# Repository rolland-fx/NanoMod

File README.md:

# NanoMod

## Main goal and design

- very low power remote sensors platform
- Modular design in layers (physical layers !) : 
	- Alim + power managment + hardware watchdog 
	- Main CPU and Radio
	- Sensors
	- Any others layer

## Few design ideas 

-  I2 Cbus as inter-layer bus (SPI vs I2C debate, go !)
	- Pintout Could be :
		* I2C (2 pins)
		* Alim (2 3.3V + 2*GND)
		* M-CPU to power managmement coms (4 Sig + 2 UART)
	- Put as 2*8 connectors (2*4 pins connectors)
- Each layer will have the sames pin-out (I2C, Alims, Vbat, and a few others signals) to be able to add as much as needed
- Main CPU may have Wifi capabilites as first time config channel.
	- Wifi could be active to enable first time boot settings
	- After that, depending of the main CPU code, it could go offline (until button press to reset seetings) 
	to keep only Lora as Radio.
- Multiple 3.3V rails, to enable or disable each ones (Main 3.3V, Main CPU 3.3V and Sensors 3.3V)
- Alim input to be able to accept anything between 3.4V and 9V, with input voltage reading
- Default Power module as : two 2.7V supercapacitor in series + solar pannel (+ wathever regulator needed between the two).
	- In test system : two 478-10027-ND + S7V7F5

## Layers :
 
 ### layer 1 : 
- ATTINY814-SSF-ND --- Power managment
- ATTINY402-SSF-ND --- Hardware watchdog 
- 3*MIC5528-3.3YMT ---  Very efficient, with OFF 3.3V switch regulator
- very low current voltage divided (/3) for battery reading

### Layer 2 : 
- RFM95W-868S2-ND  --- Lora Module 

the main CPU could be whatever we want, as much as it as SPI. First version choice could be one of this two 
- ESP8285 wathever module -- Main CPU
OR
- ESP32 (V1 or V2) whatever module  -- Main CPU

Com between MCU and Radio in SPI

### Layer 3 :
- BME680 --- Sensor
- VEML6040 --- Sensor

Could like like that :

just a lot less moche !

### MCU needed features :

- UART + 2*GPIO
- SPI
- I2C
- full 3.3V
- less than 400mW full conso
- able to be alim shutdown (when ready)

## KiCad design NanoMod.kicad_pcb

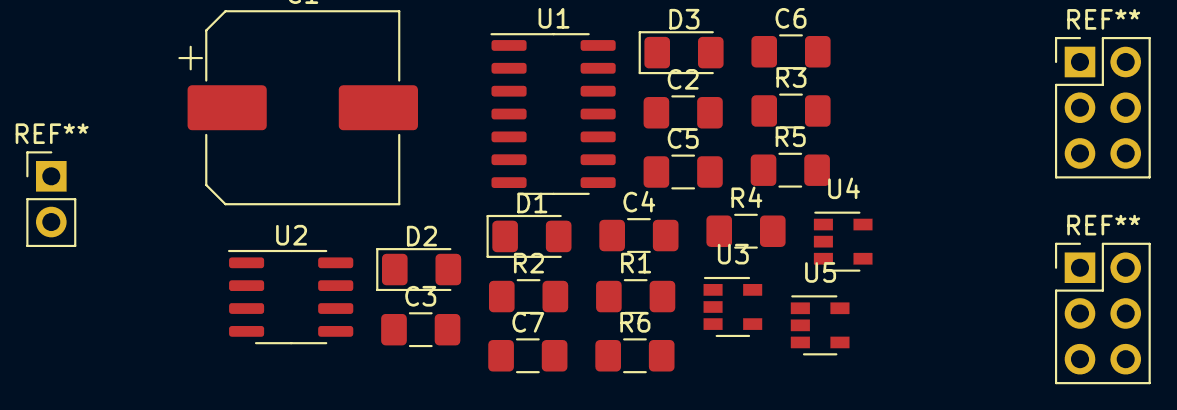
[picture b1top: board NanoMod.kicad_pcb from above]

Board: 2 copper layers, 21 parts (0 on the bottom side), 18 nets, no tracks yet.

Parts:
C1: 4700u; CP_Elec_10x12.5
C2, C3, C4, C5, C6, C7: 2.2u; C_1206_3216Metric_Pad1.42x1.75mm_HandSolder
D1, D2, D3: LED; LED_1206_3216Metric_Pad1.42x1.75mm_HandSolder
R1: 16; R_1206_3216Metric_Pad1.42x1.75mm_HandSolder
R2, R3: 100k; R_1206_3216Metric_Pad1.42x1.75mm_HandSolder
R4, R5, R6: 22k; R_1206_3216Metric_Pad1.42x1.75mm_HandSolder
U1: ATtiny804-SS; SOIC-14_3.9x8.7mm_P1.27mm
U2: ATtiny402-SS; SOIC-8_3.9x4.9mm_P1.27mm
U3, U4, U5: MIC5504-3.3YM5; SOT-23-5

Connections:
GND-bat: C1.2, C2.2, C3.2, C4.2, C5.2, C6.2, C7.2, R3.1, R4.2, R5.2, R6.2, U1.14, U2.8, U3.2, U4.2, U5.2
unnamed: C1.1, R1.2, U2.1
unnamed: C3.1, R1.1, U1.1, U3.5
unnamed: D1.1, R4.1
unnamed: D1.2, U2.3
unnamed: D2.1, R5.1
unnamed: D2.2, U1.5
unnamed: D3.1, R6.1
unnamed: D3.2, U1.4
unnamed: U1.6, U2.2
unnamed: U1.7, U2.7
unnamed: U1.8, U5.3
unnamed: U1.9, U4.3
unnamed: U2.4, U3.3
VCC-1: C7.1, U5.5
VCC-2: C5.1, U4.5
Vbat: R2.1, R3.2
Vin: C2.1, C4.1, C6.1, R2.2, U3.1, U4.1, U5.1

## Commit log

2020-05-15 Kicad schem
